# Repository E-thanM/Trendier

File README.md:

# Trendier 👗

A modern fashion social platform for analyzing outfits, discovering trends, and connecting with fashion enthusiasts.

## 🚀 Quick Start

### Option 1: Deploy to Vercel + Supabase (Recommended for Self-Hosting)
See [DEPLOYMENT.md](./DEPLOYMENT.md) for complete self-hosting guide.

### Option 2: Local Development
```bash
# Clone the repository
git clone <YOUR_GIT_URL>
cd trendier

# Install dependencies
npm install

# Copy environment variables
cp .env.example .env
# Edit .env with your Supabase credentials

# Start development server
npm run dev
```

### Option 3: Use Lovable (Original Development Environment)
Visit the [Lovable Project](https://lovable.dev/projects/6f80b55b-fee4-49fe-ab97-270c70876639) and start prompting.

## 📱 Features

- **Outfit Analysis**: AI-powered outfit rating and trend matching
- **Fashion Trends**: Browse and explore current fashion trends with 600+ hashtags
- **Social Feed**: Share outfits and engage with the community
- **Direct Messaging**: Connect with other fashion enthusiasts
- **User Profiles**: Showcase your style and preferences
- **Responsive Design**: Optimized for mobile and desktop

## 🏗️ Tech Stack

**Frontend:**
- React 18 + TypeScript
- Vite (build tool)
- TailwindCSS (styling)
- Shadcn/ui (component library)
- React Router (navigation)
- TanStack Query (data fetching)

**Backend:**
- Supabase (database, auth, storage)
- PostgreSQL (database)
- Row Level Security (RLS)
- Edge Functions (serverless API)

**AI:**
- Lovable AI API (outfit analysis)
- Gemini 2.5 Flash (vision model)

## 📁 Project Structure

```
trendier/
├── src/
│   ├── components/       # React components
│   ├── pages/           # Page components
│   ├── hooks/           # Custom React hooks
│   ├── lib/             # Utility functions
│   ├── integrations/    # Supabase client
│   └── index.css        # Global styles & design tokens
├── supabase/
│   ├── functions/       # Edge functions (backend API)
│   │   ├── analyze-outfit/   # AI outfit analysis
│   │   └── scrape-trends/    # Fashion trend scraper
│   └── migrations/      # Database schema & RLS policies
├── public/              # Static assets
├── DEPLOYMENT.md        # Self-hosting guide
├── vercel.json         # Vercel configuration
└── .env.example        # Environment variables template
```

## 🔧 Environment Variables

Required environment variables (see `.env.example`):

```env
VITE_SUPABASE_PROJECT_ID="your_project_id"
VITE_SUPABASE_URL="https://xxxxx.supabase.co"
VITE_SUPABASE_PUBLISHABLE_KEY="your_anon_key"
```

## 🗄️ Database Schema

All backend code is exposed in the repository:

**Tables** (`supabase/migrations/`):
- `profiles` - User profiles and metadata
- `outfits` - User-uploaded outfit images
- `outfit_likes` - Like/reaction system
- `outfit_comments` - Comment system
- `trends` - Fashion trend data (600+ themes)
- `user_preferences` - User style preferences
- `conversations` & `messages` - Direct messaging

**Edge Functions** (`supabase/functions/`):
- `analyze-outfit` - AI-powered outfit analysis with vision model
- `scrape-trends` - Fashion trend data aggregation

All tables protected with Row Level Security (RLS) policies.

## 🛡️ Security

- ✅ Row Level Security enabled on all tables
- ✅ Anonymous authentication for seamless onboarding
- ✅ Input validation on edge functions (Zod schemas)
- ✅ JWT-based authentication
- ✅ Secure file storage with RLS policies

## 📦 Available Scripts

```bash
npm run dev          # Start development server (localhost:8080)
npm run build        # Build for production
npm run preview      # Preview production build
npm run lint         # Run ESLint
```

## 🌐 Deployment

The app is split into two parts for independent hosting:

1. **Frontend** (Vercel/Netlify/etc): Static React app
2. **Backend** (Supabase): Database, auth, storage, edge functions

### Self-Hosting on Vercel + Supabase

**All backend functions are already exposed in this repository:**
- Database migrations: `supabase/migrations/*.sql`
- Edge functions: `supabase/functions/*/index.ts`
- Auth configuration: In migration files
- Storage policies: In migration files

**Complete deployment guide:** [DEPLOYMENT.md](./DEPLOYMENT.md)

**Quick Steps:**
1. Create your own Supabase project
2. Run migrations to set up database
3. Deploy edge functions to your Supabase project
4. Deploy frontend to Vercel with environment variables
5. Configure auth redirect URLs

### Deploy via Lovable (Easiest)

Simply open [Lovable](https://lovable.dev/projects/6f80b55b-fee4-49fe-ab97-270c70876639) and click Share → Publish.

## 📱 Responsive Design

The app automatically adapts to different screen sizes:

- **Mobile View** (< 768px): 
  - Bottom navigation bar
  - Single-column layout
  - Touch-optimized interactions
  - Mobile-first card designs

- **Desktop View** (≥ 768px):
  - Sidebar navigation
  - Multi-column grid layouts
  - Hover interactions
  - Expanded content display

Vercel (or any static host) serves the built files, and CSS media queries handle responsive behavior automatically.

## 🔌 Backend API Endpoints

When self-hosting, your edge functions will be available at:

```
POST https://YOUR_PROJECT_ID.supabase.co/functions/v1/analyze-outfit
POST https://YOUR_PROJECT_ID.supabase.co/functions/v1/scrape-trends
```

See [DEPLOYMENT.md](./DEPLOYMENT.md) for API documentation and examples.

## 📄 License

This project is open source and available under the MIT License.

## 🤝 Contributing

Contributions are welcome! Please feel free to submit a Pull Request.

## 📞 Support

- **Self-hosting help**: See [DEPLOYMENT.md](./DEPLOYMENT.md)
- **Supabase docs**: [supabase.com/docs](https://supabase.com/docs)
- **Vercel docs**: [vercel.com/docs](https://vercel.com/docs)
- **Lovable docs**: [docs.lovable.dev](https://docs.lovable.dev)

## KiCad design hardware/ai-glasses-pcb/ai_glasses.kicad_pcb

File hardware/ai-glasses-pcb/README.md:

# AI Glasses – Temple PCB

4-layer KiCad project for the electronics in one temple arm of the AI glasses:

- ESP32-S3-WROOM-1 (N16R8)
- DVP camera connector (OV2640 / OV5640)
- I2S MEMS microphone
- USB-C Li-Po charging
- I2S amplifier driving a bone-conduction transducer behind the ear

| File | What it is |
|---|---|
| `ai_glasses.kicad_pro` | open this in KiCad 7+ |
| `ai_glasses.kicad_sch` / `.kicad_pcb` | schematic and routed board |
| `fab/` | Gerbers (+ zip), drill files, pick-and-place, BOM, schematic and assembly PDFs |
| `docs/DESIGN.md` | design notes: shape and anthropometry, power tree, pin map, stack-up, verification, bring-up checklist |
| `VERIFICATION.txt` | output of `scripts/check_design.py` |
| `scripts/` | generators; `design.py` is the single source of truth |

**Note:** the Raspberry Pi Zero camera (MIPI CSI-2) can't connect to an
ESP32-S3. The board uses the pin-compatible-size DVP camera modules instead.
See `docs/DESIGN.md` §2.

## Opening it in KiCad and checking it

1. Install **KiCad 7 or newer**. If you open it in KiCad 8 or 9 and save,
   the files are upgraded and older versions can no longer open them.
2. Open `ai_glasses.kicad_pro`. Keep the whole folder together: the project's
   own symbol/footprint libraries (`AI_Glasses.*`) are found through
   `${KIPRJMOD}`.
3. **Schematic:** Inspect → Electrical Rules Checker → Run ERC. Expect
   0 errors. "Symbol doesn't match library" warnings are harmless; don't
   bulk-update symbols from the library.
4. **PCB:**
   - Press **B** to refill zones.
   - Run **Inspect → Design Rules Checker** with *Refill all zones*
     ticked. Expect 0 errors and 0 unconnected items. The custom rules
     in `ai_glasses.kicad_dru` load automatically.
   - Run **Tools → Update PCB from Schematic** (F8). It should list no
     changes; if it does, cancel.
5. **3D view** (Alt+3): the footprints reference
   `${KICAD7_3DMODEL_DIR}` / `${KICAD6_3DMODEL_DIR}`. On KiCad 8/9, if the
   models are missing, add those names under Preferences → Configure Paths,
   pointing at the same folder as your `KICAD8_`/`KICAD9_3DMODEL_DIR`. This
   only affects the 3D view.
6. **Fab files:** open `fab/gerbers/` in KiCad's Gerber Viewer. To order,
   upload `fab/ai_glasses-gerbers.zip`: 4 layers, 1.0 mm thick,
   1 oz outer / 0.5 oz inner. For assembly, add `fab/ai_glasses-BOM.csv`
   and `fab/ai_glasses-pos.csv`.

### Automated checks (optional)
Needs KiCad's Python module (`pcbnew`) and `pip install sexpdata numpy`.

```
cd scripts
python3 check_design.py   # 600+ checks: netlist match, wiring, links, ERC-style, DRC, placement
python3 check_wiring.py   # schematic wires/labels/no-connects only
```

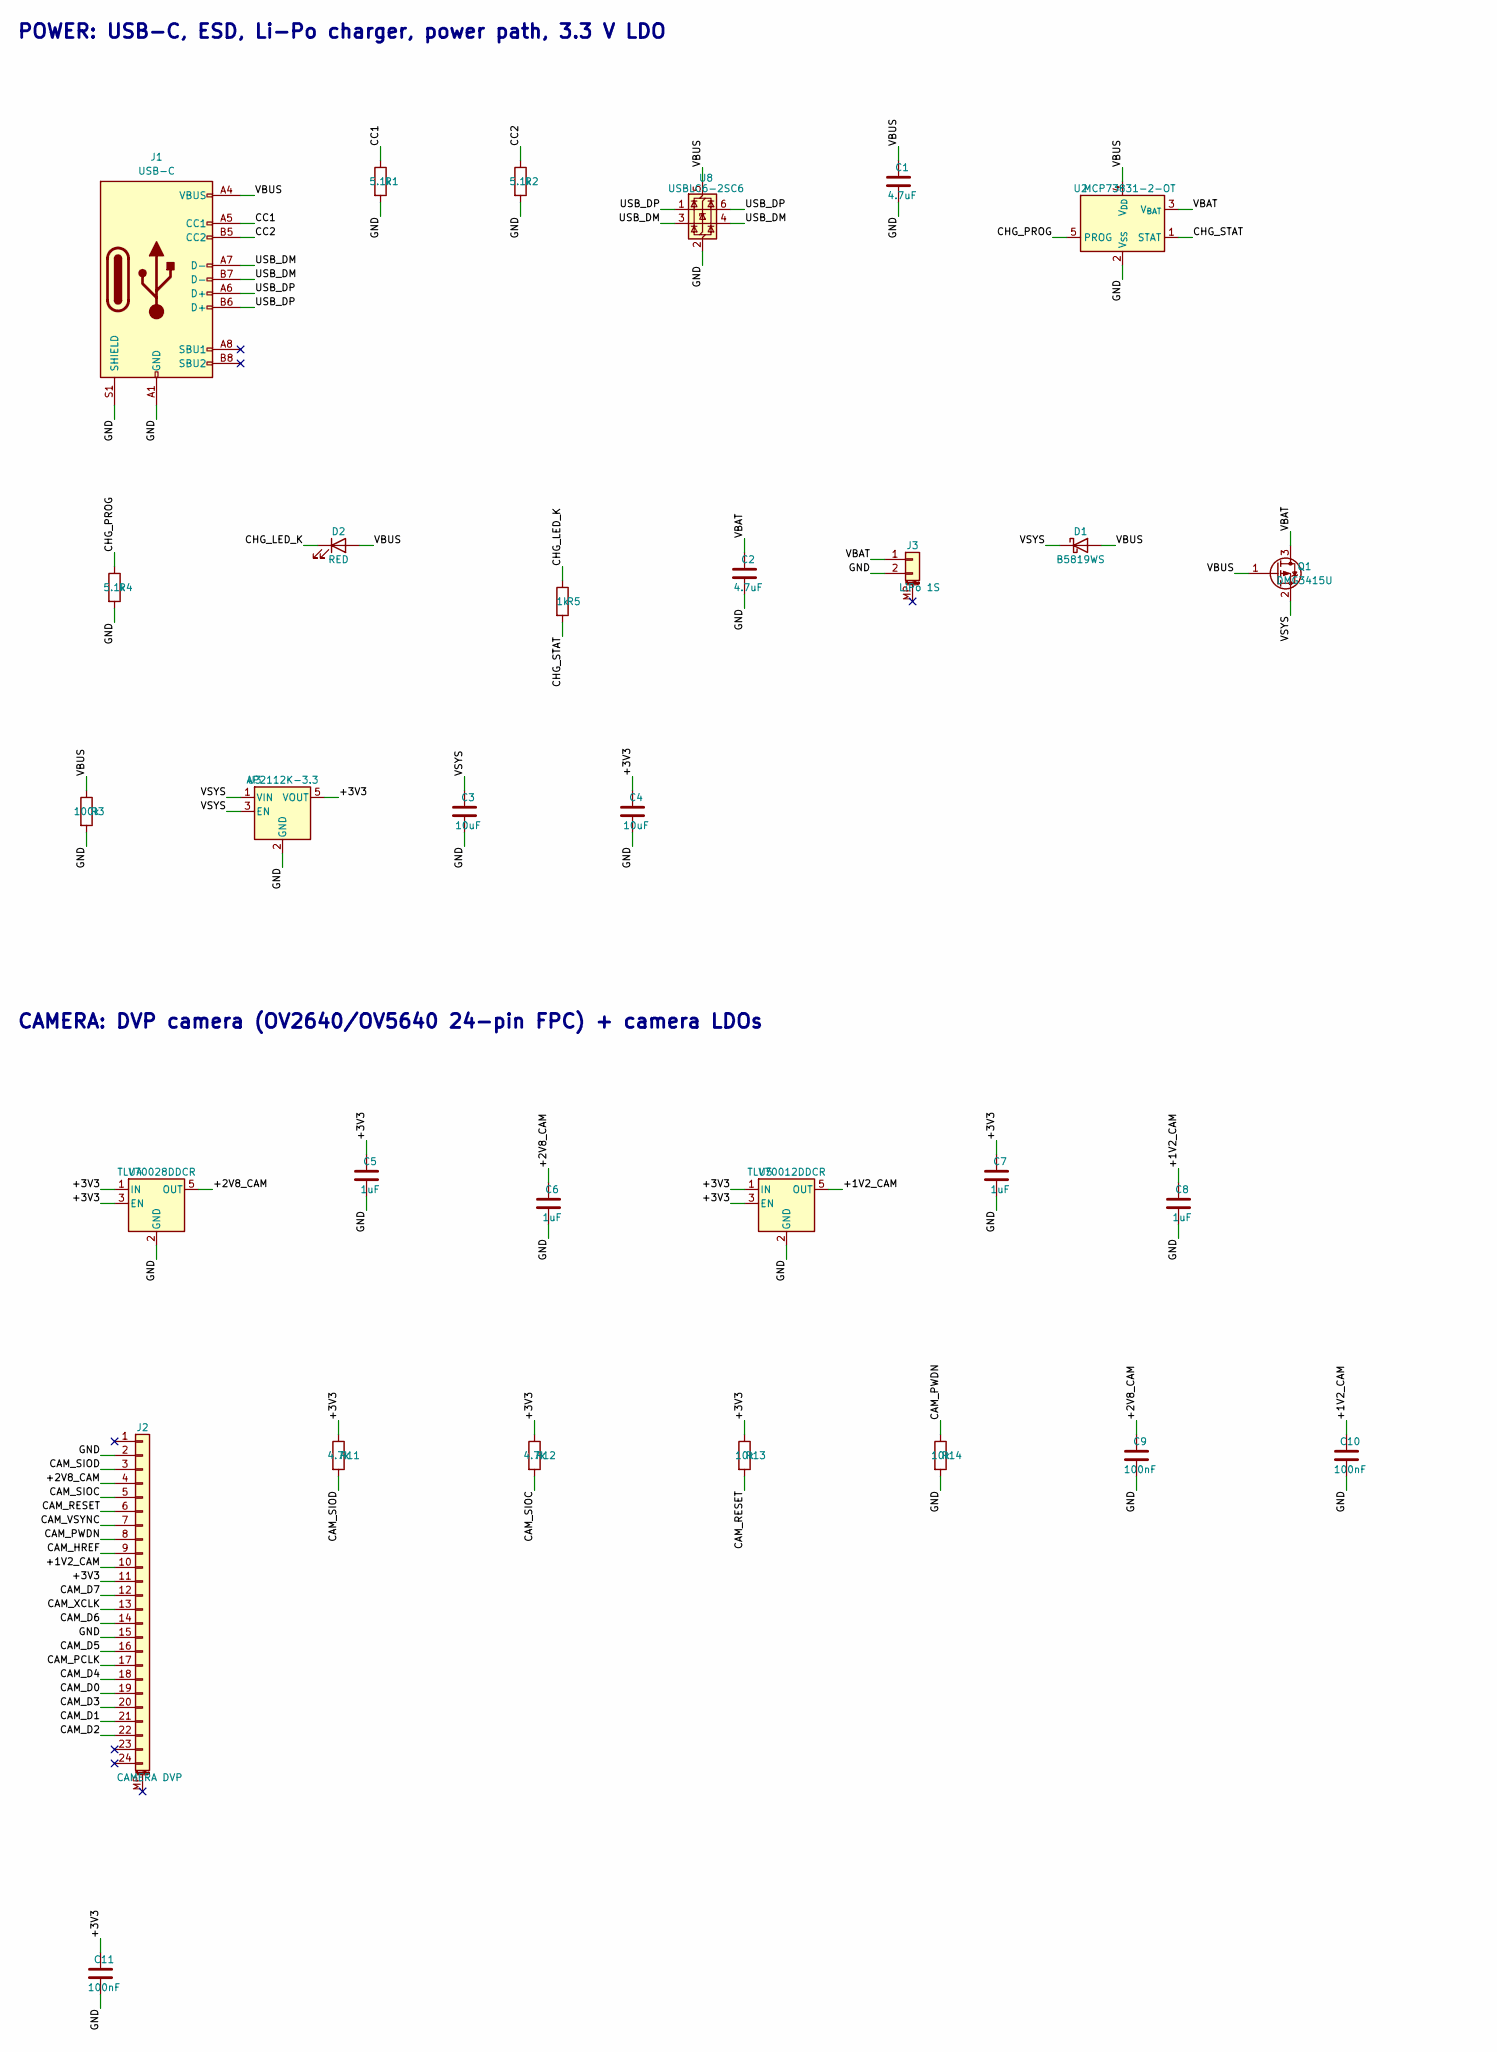
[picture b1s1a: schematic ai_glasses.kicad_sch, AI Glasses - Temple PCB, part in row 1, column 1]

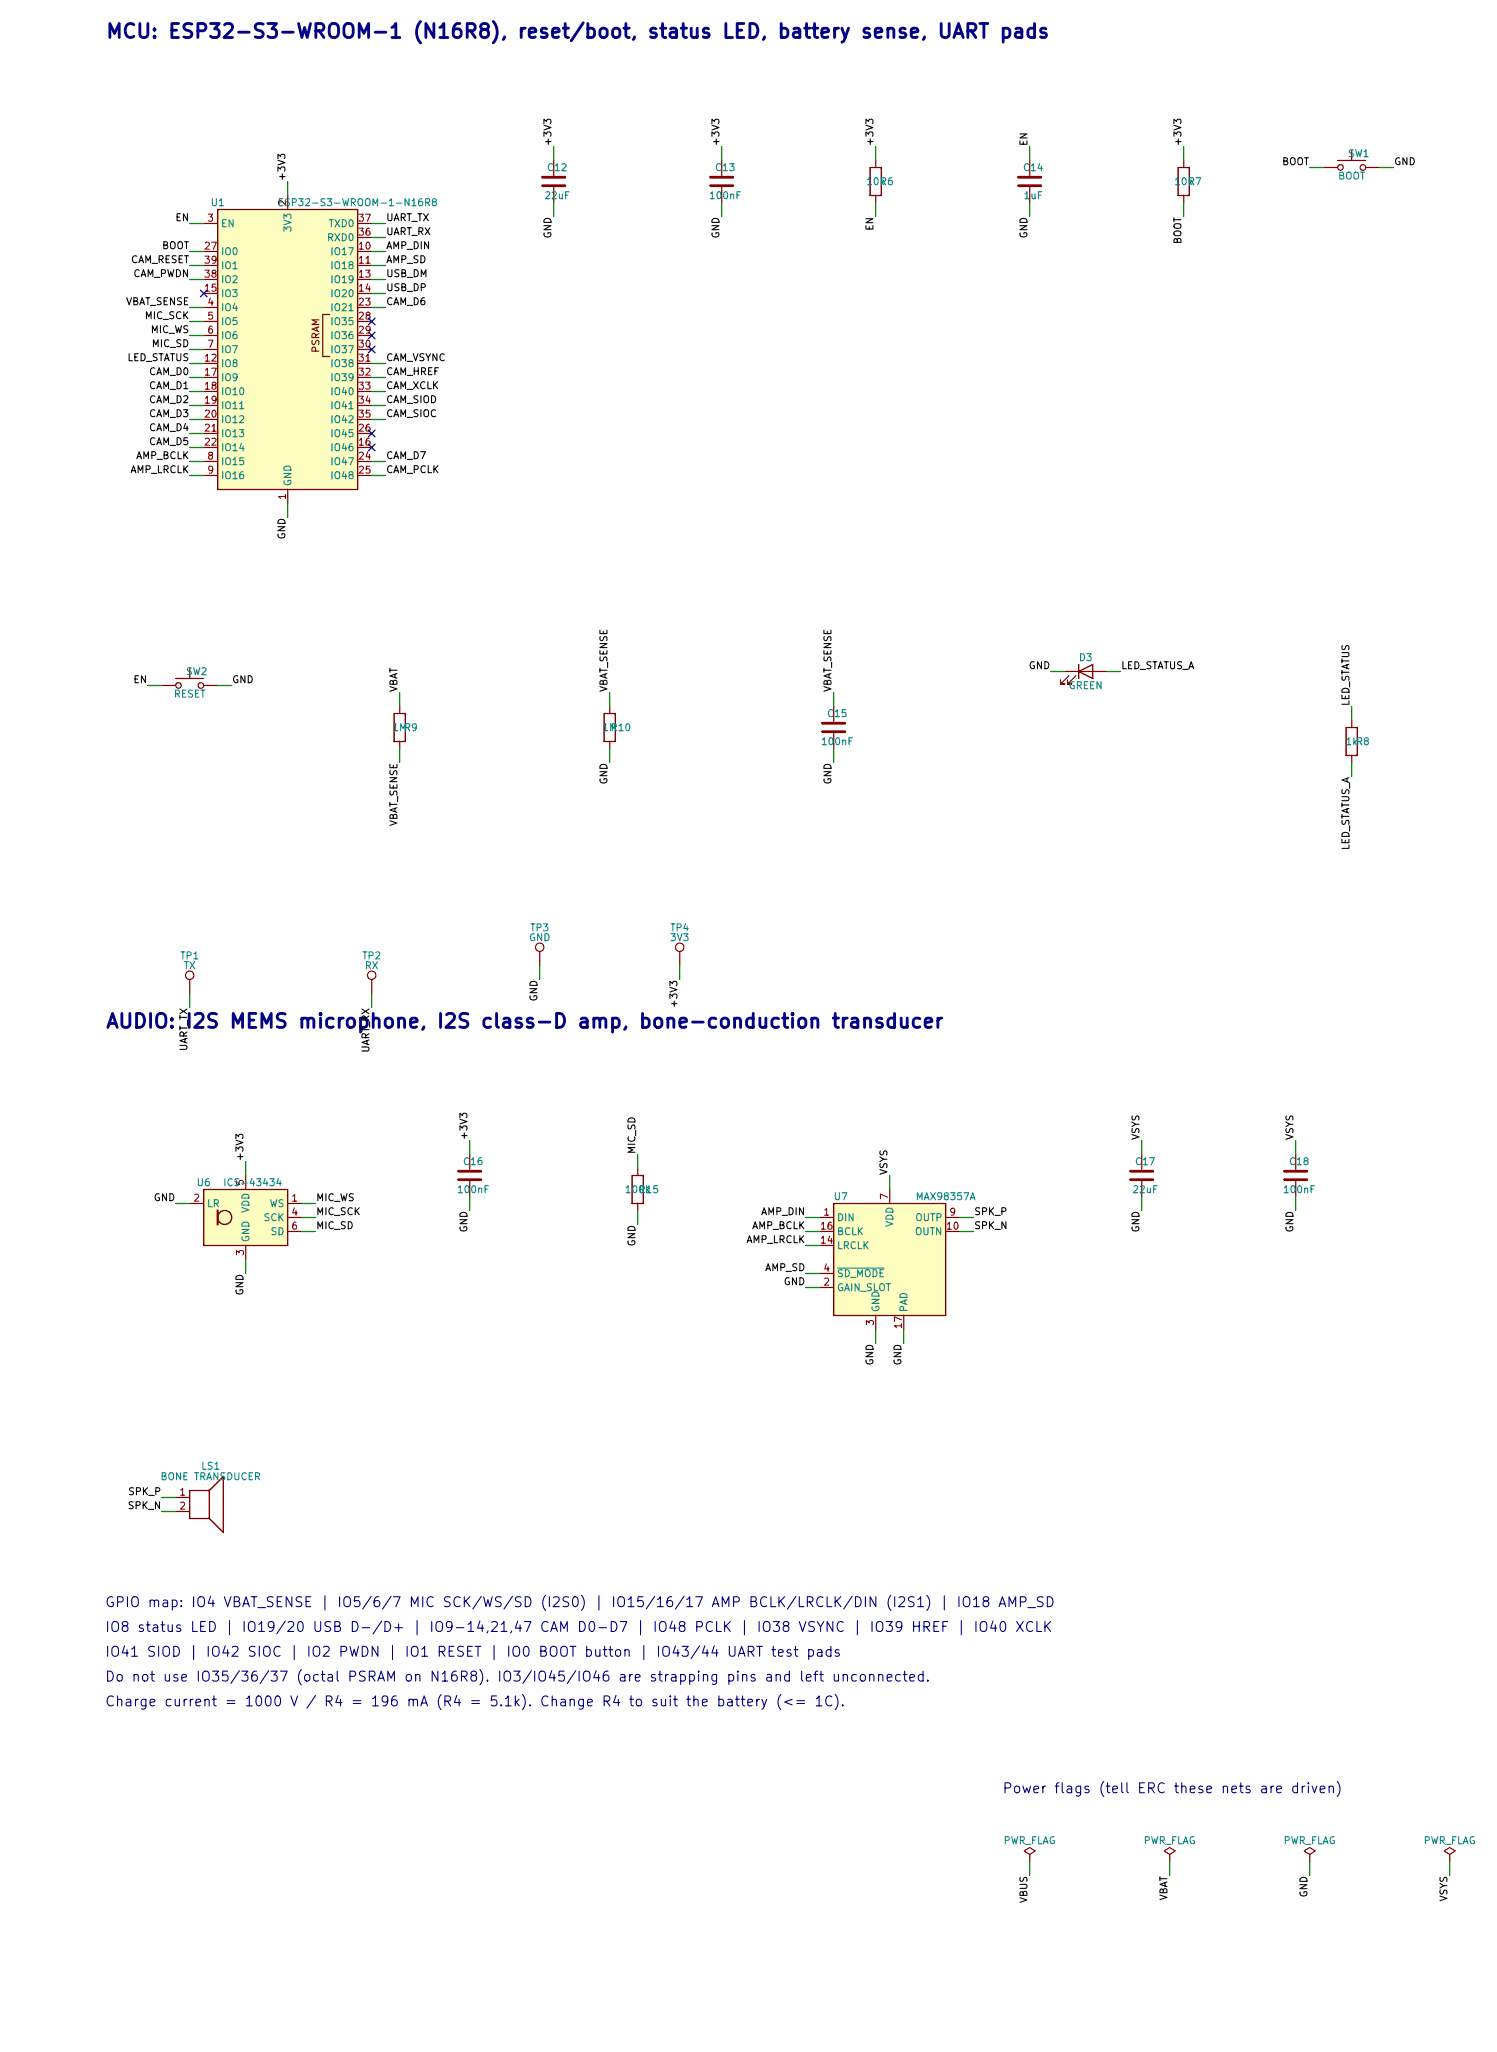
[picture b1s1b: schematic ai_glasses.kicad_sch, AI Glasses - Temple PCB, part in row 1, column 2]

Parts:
C1, C2: 4.7uF; C_0603_1608Metric
C3, C4: 10uF; C_0603_1608Metric
C5, C6, C7, C8, C14: 1uF; C_0402_1005Metric
C9, C10, C11, C13, C15, C16, C18: 100nF; C_0402_1005Metric
C12, C17: 22uF; C_0805_2012Metric
D1: B5819WS; D_SOD-323; MPN B5819WS
D2: RED; LED_0603_1608Metric
D3: GREEN; LED_0603_1608Metric
J1: USB-C; USB_C_Receptacle_GCT_USB4105-xx-A_16P_TopMnt_Horizontal; MPN GCT USB4105-GF-A
J2: CAMERA DVP; Hirose_FH12-24S-0.5SH_1x24-1MP_P0.50mm_Horizontal; MPN Hirose FH12-24S-0.5SH(55)
J3: LiPo 1S; JST_SH_SM02B-SRSS-TB_1x02-1MP_P1.00mm_Horizontal; MPN JST SM02B-SRSS-TB
LS1: BONE TRANSDUCER; BoneTransducer_SolderPads; MPN 8 ohm bone-conduction exciter (e.g. 13x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
Q1: DMG3415U; SOT-23; MPN Diodes DMG3415U-7
R1, R2, R4: 5.1k; R_0402_1005Metric
R3, R15: 100k; R_0402_1005Metric
R5, R8: 1k; R_0402_1005Metric
R6, R7, R13, R14: 10k; R_0402_1005Metric
R9, R10: 1M; R_0402_1005Metric
R11, R12: 4.7k; R_0402_1005Metric
SW1: BOOT; SW_SPST_B3U-1000P; MPN Omron B3U-1000P
SW2: RESET; SW_SPST_B3U-1000P; MPN Omron B3U-1000P
TP1: TX; TestPoint_Pad_D1.0mm
TP2: RX; TestPoint_Pad_D1.0mm
TP3: GND; TestPoint_Pad_D1.0mm
TP4: 3V3; TestPoint_Pad_D1.0mm
U1: ESP32-S3-WROOM-1-N16R8; ESP32-S3-WROOM-1; MPN Espressif ESP32-S3-WROOM-1-N16R8
U2: MCP73831-2-OT; SOT-23-5; MPN Microchip MCP73831T-2ACI/OT
U3: AP2112K-3.3; SOT-23-5; MPN Diodes AP2112K-3.3TRG1
U4: TLV70028DDCR; SOT-23-5; MPN TI TLV70028DDCR
U5: TLV70012DDCR; SOT-23-5; MPN TI TLV70012DDCR
U6: ICS-43434; InvenSense_ICS-43434-6_3.5x2.65mm; MPN TDK InvenSense ICS-43434
U7: MAX98357A; TQFN-16-1EP_3x3mm_P0.5mm_EP1.23x1.23mm_ThermalVias; MPN Analog Devices MAX98357AETE+T
U8: USBLC6-2SC6; SOT-23-6; MPN STMicro USBLC6-2SC6

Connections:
+1V2_CAM: C8.1, C10.1, J2.10, U5.5 (OUT)
+2V8_CAM: C6.1, C9.1, J2.4, U4.5 (OUT)
+3V3: C4.1, C5.1, C7.1, C11.1, C12.1, C13.1, C16.1, J2.11, R6.1, R7.1, R11.1, R12.1, R13.1, TP4.1, U1.2 (3V3), U3.5 (VOUT), U4.1 (IN), U4.3 (EN), U5.1 (IN), U5.3 (EN), U6.5 (VDD)
AMP_BCLK: U1.8 (IO15), U7.16 (BCLK)
AMP_DIN: U1.10 (IO17), U7.1 (DIN)
AMP_LRCLK: U1.9 (IO16), U7.14 (LRCLK)
AMP_SD: U1.11 (IO18), U7.4 (~SD_MODE)
BOOT: R7.2, SW1.1, U1.27 (IO0)
CAM_D0: J2.19, U1.17 (IO9)
CAM_D1: J2.21, U1.18 (IO10)
CAM_D2: J2.22, U1.19 (IO11)
CAM_D3: J2.20, U1.20 (IO12)
CAM_D4: J2.18, U1.21 (IO13)
CAM_D5: J2.16, U1.22 (IO14)
CAM_D6: J2.14, U1.23 (IO21)
CAM_D7: J2.12, U1.24 (IO47)
CAM_HREF: J2.9, U1.32 (IO39)
CAM_PCLK: J2.17, U1.25 (IO48)
CAM_PWDN: J2.8, R14.1, U1.38 (IO2)
CAM_RESET: J2.6, R13.2, U1.39 (IO1)
CAM_SIOC: J2.5, R12.2, U1.35 (IO42)
CAM_SIOD: J2.3, R11.2, U1.34 (IO41)
CAM_VSYNC: J2.7, U1.31 (IO38)
CAM_XCLK: J2.13, U1.33 (IO40)
CC1: J1.A5 (CC1), R1.1
CC2: J1.B5 (CC2), R2.1
CHG_LED_K: D2.1 (K), R5.1
CHG_PROG: R4.1, U2.5 (PROG)
CHG_STAT: R5.2, U2.1 (STAT)
EN: C14.1, R6.2, SW2.1, U1.3 (EN)
GND: C1.2, C2.2, C3.2, C4.2, C5.2, C6.2, C7.2, C8.2, C9.2, C10.2, C11.2, C12.2, C13.2, C14.2, C15.2, C16.2, C17.2, C18.2, D3.1 (K), J1.A1 (GND), J1.A12 (GND), J1.B1 (GND), J1.B12 (GND), J1.S1 (SHIELD), J2.2, J2.15, J3.2, R1.2, R2.2, R3.2, R4.2, R10.2, R14.2, R15.2, SW1.2, SW2.2, TP3.1, U1.1 (GND), U1.40 (GND), U1.41 (GND), U2.2 (V_{SS}), U3.2 (GND), U4.2 (GND), U5.2 (GND), U6.2 (LR), U6.3 (GND), U7.2 (GAIN_SLOT), U7.3 (GND), U7.11 (GND), U7.15 (GND), U7.17 (PAD), U8.2 (GND)
LED_STATUS: R8.1, U1.12 (IO8)
LED_STATUS_A: D3.2 (A), R8.2
MIC_SCK: U1.5 (IO5), U6.4 (SCK)
MIC_SD: R15.1, U1.7 (IO7), U6.6 (SD)
MIC_WS: U1.6 (IO6), U6.1 (WS)
SPK_N: LS1.2, U7.10 (OUTN)
SPK_P: LS1.1, U7.9 (OUTP)
UART_RX: TP2.1, U1.36 (RXD0)
UART_TX: TP1.1, U1.37 (TXD0)
USB_DM: J1.A7 (D-), J1.B7 (D-), U1.13 (IO19), U8.3 (I/O2), U8.4 (I/O2)
USB_DP: J1.A6 (D+), J1.B6 (D+), U1.14 (IO20), U8.1 (I/O1), U8.6 (I/O1)
VBAT: C2.1, J3.1, Q1.3 (D), R9.1, U2.3 (V_{BAT})
VBAT_SENSE: C15.1, R9.2, R10.1, U1.4 (IO4)
VBUS: C1.1, D1.2 (A), D2.2 (A), J1.A4 (VBUS), J1.A9 (VBUS), J1.B4 (VBUS), J1.B9 (VBUS), Q1.1 (G), R3.1, U2.4 (V_{DD}), U8.5 (VBUS)
VSYS: C3.1, C17.1, C18.1, D1.1 (K), Q1.2 (S), U3.1 (VIN), U3.3 (EN), U7.7 (VDD), U7.8 (VDD)

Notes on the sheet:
POWER: USB-C, ESD, Li-Po charger, power path, 3.3 V LDO
MCU: ESP32-S3-WROOM-1 (N16R8), reset/boot, status LED, battery sense, UART pads
CAMERA: DVP camera (OV2640/OV5640 24-pin FPC) + camera LDOs
AUDIO: I2S MEMS microphone, I2S class-D amp, bone-conduction transducer
Power flags (tell ERC these nets are driven)
GPIO map: IO4 VBAT_SENSE | IO5/6/7 MIC SCK/WS/SD (I2S0) | IO15/16/17 AMP BCLK/LRCLK/DIN (I2S1) | IO18 AMP_SD
IO8 status LED | IO19/20 USB D-/D+ | IO9-14,21,47 CAM D0-D7 | IO48 PCLK | IO38 VSYNC | IO39 HREF | IO40 XCLK
IO41 SIOD | IO42 SIOC | IO2 PWDN | IO1 RESET | IO0 BOOT button | IO43/44 UART test pads
Do not use IO35/36/37 (octal PSRAM on N16R8). IO3/IO45/IO46 are strapping pins and left unconnected.
Charge current = 1000 V / R4 = 196 mA (R4 = 5.1k). Change R4 to suit the battery (<= 1C).

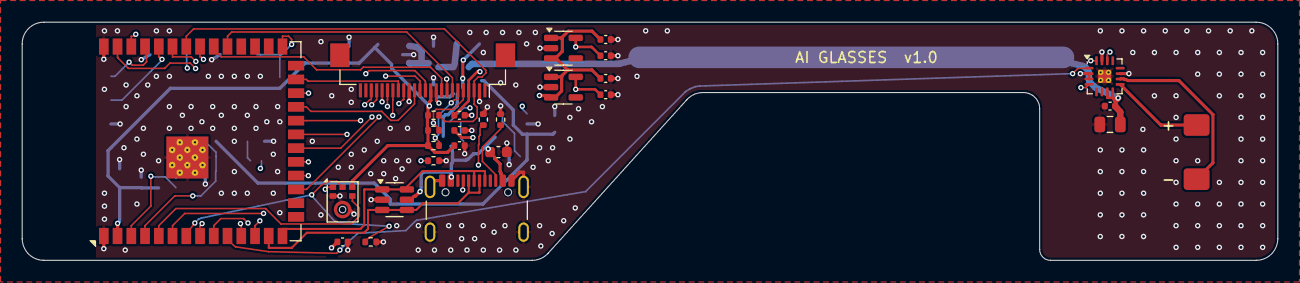
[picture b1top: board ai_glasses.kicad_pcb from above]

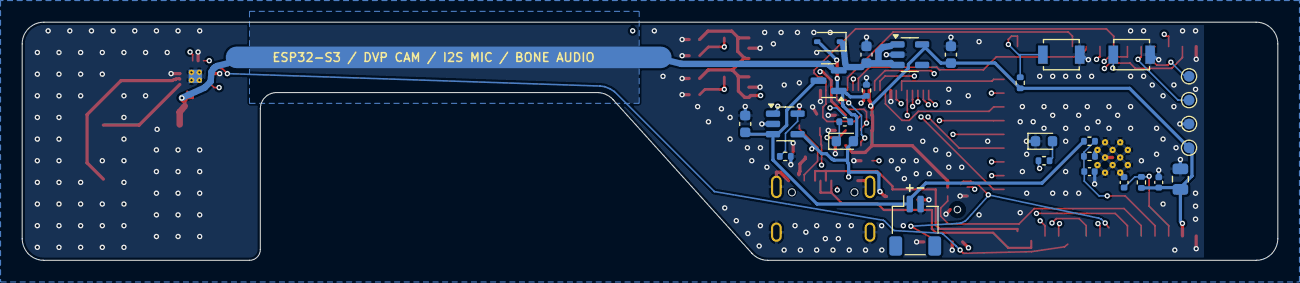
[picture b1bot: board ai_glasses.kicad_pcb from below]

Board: 4 copper layers, 116.0 x 22.0 mm, 55 parts (28 on the bottom side), 46 nets.

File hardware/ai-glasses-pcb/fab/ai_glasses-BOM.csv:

Qty,References,Value,Footprint,Part / MPN,Side,Notes
2,C1 C2,4.7uF,C_0603_1608Metric,"X5R/X7R MLCC, >= 10 V",Bottom/Top,
2,C12 C17,22uF,C_0805_2012Metric,"X5R/X7R MLCC, >= 10 V",Bottom/Top,
7,C9 C10 C11 C13 C15 C16 C18,100nF,C_0402_1005Metric,"X5R/X7R MLCC, >= 10 V",Bottom/Top,
2,C3 C4,10uF,C_0603_1608Metric,"X5R/X7R MLCC, >= 10 V",Bottom,
5,C5 C6 C7 C8 C14,1uF,C_0402_1005Metric,"X5R/X7R MLCC, >= 10 V",Bottom/Top,
1,D1,B5819WS,D_SOD-323,B5819WS,Bottom,USB -> system power path
1,D2,RED,LED_0603_1608Metric,0603 LED,Bottom,Charging indicator
1,D3,GREEN,LED_0603_1608Metric,0603 LED,Bottom,Status LED
1,J1,USB-C,USB_C_Receptacle_GCT_USB4105-xx-A_16P_TopMnt_Horizontal,GCT USB4105-GF-A,Top,"USB-C 2.0 receptacle, charging + native USB programming"
1,J2,CAMERA DVP,Hirose_FH12-24S-0.5SH_1x24-1MP_P0.50mm_Horizontal,Hirose FH12-24S-0.5SH(55),Top,24-pin 0.5 mm FPC for OV2640 / OV5640 DVP camera
1,J3,LiPo 1S,JST_SH_SM02B-SRSS-TB_1x02-1MP_P1.00mm_Horizontal,JST SM02B-SRSS-TB,Bottom,"Battery connector (JST-SH 1 mm). Pin1 = +, Pin2 = -"
1,LS1,BONE TRANSDUCER,BoneTransducer_SolderPads,"8 ohm bone-conduction exciter (e.g. 13x13 mm, 1 W)",Top,Bone conduction transducer solder pads
1,Q1,DMG3415U,SOT-23,Diodes DMG3415U-7,Bottom,Battery -> system ideal-diode switch (off when USB present)
3,R1 R2 R4,5.1k,R_0402_1005Metric,"Yageo RC0402FR-07 series (1%, 1/16 W)",Bottom/Top,
2,R11 R12,4.7k,R_0402_1005Metric,"Yageo RC0402FR-07 series (1%, 1/16 W)",Top,
2,R3 R15,100k,R_0402_1005Metric,"Yageo RC0402FR-07 series (1%, 1/16 W)",Bottom/Top,
2,R5 R8,1k,R_0402_1005Metric,"Yageo RC0402FR-07 series (1%, 1/16 W)",Bottom,
4,R6 R7 R13 R14,10k,R_0402_1005Metric,"Yageo RC0402FR-07 series (1%, 1/16 W)",Bottom/Top,
2,R9 R10,1M,R_0402_1005Metric,"Yageo RC0402FR-07 series (1%, 1/16 W)",Bottom,
1,SW1,BOOT,SW_SPST_B3U-1000P,Omron B3U-1000P,Bottom,Boot / user button (IO0)
1,SW2,RESET,SW_SPST_B3U-1000P,Omron B3U-1000P,Bottom,Reset button (EN)
1,TP1,TX,TestPoint_Pad_D1.0mm,(bare pad - not assembled),Bottom,UART0 TX test pad
1,TP2,RX,TestPoint_Pad_D1.0mm,(bare pad - not assembled),Bottom,UART0 RX test pad
1,TP3,GND,TestPoint_Pad_D1.0mm,(bare pad - not assembled),Bottom,GND test pad
1,TP4,3V3,TestPoint_Pad_D1.0mm,(bare pad - not assembled),Bottom,3V3 test pad
1,U1,ESP32-S3-WROOM-1-N16R8,ESP32-S3-WROOM-1,Espressif ESP32-S3-WROOM-1-N16R8,Top,"Wi-Fi/BLE MCU, 16 MB flash, 8 MB octal PSRAM"
1,U2,MCP73831-2-OT,SOT-23-5,Microchip MCP73831T-2ACI/OT,Bottom,"Single-cell Li-Po charger, 196 mA (R4)"
1,U3,AP2112K-3.3,SOT-23-5,Diodes AP2112K-3.3TRG1,Bottom,3.3 V / 600 mA main LDO
1,U4,TLV70028DDCR,SOT-23-5,TI TLV70028DDCR,Top,Camera AVDD 2.8 V LDO
1,U5,TLV70012DDCR,SOT-23-5,TI TLV70012DDCR,Top,Camera DVDD 1.2 V LDO
1,U6,ICS-43434,InvenSense_ICS-43434-6_3.5x2.65mm,TDK InvenSense ICS-43434,Top,"I2S MEMS microphone, bottom port (hole through PCB)"
1,U7,MAX98357A,TQFN-16-1EP_3x3mm_P0.5mm_EP1.23x1.23mm_ThermalVias,Analog Devices MAX98357AETE+T,Top,"3.2 W I2S class-D amplifier, gain 12 dB (GAIN_SLOT to GND)"
1,U8,USBLC6-2SC6,SOT-23-6,STMicro USBLC6-2SC6,Top,USB ESD protection

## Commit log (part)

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2025-11-05 [skip lovable] Use tech stack vite_react_shadcn_ts_20250728_minor
2025-11-05 Refactor UI for modern look
2025-11-07 Refactor: Implement AI analysis and update styling
    This commit introduces AI-powered outfit analysis and refactors the application's styling to be more modern and professional.
    Key changes include:
    - **Color Scheme Update**: Implemented a complementary green and blue color scheme in `src/index.css` for a sleeker, more professional look.
    - **AI Outfit Analysis**: Integrated Lovable AI for outfit analysis. The `analyze-outfit` edge function now processes uploaded images and provides ratings, trend matches, and style analysis.
    - **Trend Scraper**: Implemented a `scrape-trends` edge function to fetch and store current fashion trends, which are then used by the AI analyzer.
    - **Profile Page Enha
2025-11-07 Enhance feed with Instagram-like features
    Add stories bar, double-tap to like functionality, and improve outfit card display to mimic Instagram's feed experience. Also includes a fix for a build error by adding the `react-is` dependency.
2025-11-07 Implement comment and share functionality
    Add functionality to the comment and share buttons on outfit posts. This includes creating a `CommentsDrawer` component for viewing and adding comments, and a `ShareDialog` component for sharing opti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
2025-11-07 Position comments dialog at bottom
    Move the floating comments dialog to the bottom of the screen for desktop users. The dialog maintains a compact and visually appealing design.
2025-11-07 Align headers at the top
    Align the sidebar header with the main header to ensure they align at the top when scrolled. This involves setting a consistent height and vertical alignment for both elements.
2025-11-07 Refactor settings tab
    Switch up the settings tab to include account information, contact us form, and privacy preferences. This refactor provides a more intuitive and valuable user experience.
2025-11-07 Hide FeedHeader on desktop, add messages/notifications to settings
    The FeedHeader component is now hidden on desktop screens (`md:hidden`) and will only appear on mobile devices. The messages and notifications sections have been integrated into the `SettingsSheet` c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
2025-11-07 Refactor messages page layout and functionality
    Improve spacing on the messages page to fit perfectly on a single desktop view. Make the send button functional, allowing users to send messages within a conversation.
2025-11-07 Fix messaging error and make survey collapsible
    The RLS policy for conversation_participants was causing infinite recursion, which has been fixed. The PreferencesSurvey component has been made collapsible, with a button to start the quiz. The surv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
2025-11-07 Implement followers section and public followers setting
    This commit introduces the followers section, allowing users to view their followers and who they are following. It also adds a setting to control the visibility of followers, making the section publ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
2025-11-07 Fix settings icon positioning
    Adjust the flex alignment and positioning of the settings icon on the profile page to ensure it is correctly aligned with other profile elements.
2025-11-07 Fix security vulnerabilities
    Add input validation and email redirect configuration to address security vulnerabilities.
2025-11-07 Fix settings icon positioning
    Adjusted the layout of the profile header to ensure the settings icon remains correctly positioned and constrained within its container, preventing it from appearing out of place on the right side.
2025-11-07 Update site info
    Edited UI in Lovable
2025-11-07 Add duplicate username/email validation
    Add validation to the login page to check for existing usernames and emails before account creation. If a duplicate is found, a user-friendly toast message will be displayed.
2025-11-07 Fix flickering messages and RLS policy
    The AI addressed critical issues in the messaging feature:
    - Resolved button nesting errors in `src/pages/Messages.tsx` that caused message flickering and disappearing.
    - Updated the RLS policy for the `conversations` table to `FOR INSERT TO authenticated WITH CHECK (auth.uid() IS NOT NULL)` to ensure users can create conversations.
    - Added a "Back" button to the messages page to allow users to exit problematic conversations.
2025-11-07 Fix message creation RLS policy
    Implemented a SECURITY DEFINER function `create_conversation_for_users` to handle conversation creation. This function bypasses RLS policies for the `conversations` table but includes internal checks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
2025-11-07 Add fullscreen image viewer
    Implement a fullscreen image viewer for outfit posts, similar to Instagram's functionality. This includes creating a new `FullscreenImageViewer` component and integrating it into the `OutfitCard` com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
2025-11-08 Add X button to trend chart popup
    Add an X button to the trend detail modal to allow users to close the popup charts. The button is styled similarly to the one in `FullscreenImageViewer.tsx` and is positioned in the top-right corner 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
2025-11-08 Add clickable hashtags to Analyzer page
    Implement functionality to make hashtags on the Analyzer page clickable. Clicking a hashtag will now fetch detailed trend information from the database and display it in a modal using the existing Tr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
2025-11-08 Expand trend tracking and enable real-time updates
    This commit expands the list of tracked fashion hashtags in the scraper to over 100, providing more comprehensive data research and topics. It also enables real-time updates for the trends section by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
2025-11-08 Fix guest profile page display
    Ensure sign up/login prompts are displayed for guests and unauthenticated users when they attempt to access the profile page. This resolves an issue where these users might see a blank page or an inc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
2025-11-09 Fix vertical alignment in sidebar
    Ensure consistent vertical alignment and height for all sidebar menu items by removing the SidebarMenuButton wrapper and applying uniform styling directly to the elements. This resolves lingering ver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
2025-11-09 Fix security vulnerabilities
    Address critical security issues including an unprotected edge function, authentication bypass via guest mode, and missing input validation in the analyze-outfit function.
2025-11-09 Make bottom nav highlight constant
    Ensure the active tab in the mobile bottom navigation bar is always highlighted green, regardless of hover state. This change applies consistent styling to all navigation items based on the current r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
2025-11-09 Add caching to trend scraper
    Implement a caching mechanism for the trend scraper to store discovered trends for 7 days. This reduces the need for frequent Serper API calls and preserves the request quota.
    Additionally, this commit addresses the user's concern about no API usage being detected on Serper. It clarifies that the "analyzer feature" is for user outfit photos and is separate from the trend s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
2025-11-09 Add error handling to analyze-outfit function
    Improve error handling in the analyze-outfit edge function to provide more detailed logs when API calls fail. This will help in diagnosing issues with Gemini API responses for search term extraction 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
2025-11-10 Add profile picture upload
    Enable uploading and displaying a profile avatar
    - Integrates avatar upload flow on /profile
    - Adds storage-backed avatar upload using Supabase
    - Updates Profile UI to show and replace avatar
    - Includes removal of old avatar and update to user profile avatar_url
2025-11-10 Mark unread badge read
    Improve unread badge handling by updating markAsRead to rely on latest message timestamp and propagate reads more reliably. Ensures badge disappears when all conversations are viewed and prepares bac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
2025-11-10 Update analyzer to 100-point scale
    Converts backend rating from 1-10 to 1-100 and updates analyzer to display /100 accordingly. Adjusts edge function prompt and rate handling to align with the new scale.
2025-11-10 Link TikTok trends with photo analyzer
    Integrate TikTok trend data into the outfit analyzer by:
    - Fetching current TikTok trend items from the tiktok_videos and tiktok_detected_items tables
    - Calculating and displaying a TikTok trend match score for outfits
    - Showing matching TikTok items and example videos alongside analyzer results
    - Extending Analyzer.tsx UI to present TikTok trend data and matches
    - Ensuring seamless UX when cross-referencing trends with uploaded photos
2025-11-10 Set up automated TikTok Scraping
    Implement cron-based background scraping, verify real video content analysis, speed up analyzer, merge UI, and complete end-to-end testing for TikTok trends integration.
2025-11-10 Fix base64 conversion loop in outfit analyzer
    Replace problematic base64 conversion using spread operator with iterative byte-to-base64 encoding in analyze-outfit to prevent stack overflow on large images; deploy fixed edge function and ensure n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
2025-11-10 Improve TikTok video data usage and Google Trends UI
2025-11-10 Reduce TikTok visual match to 3 videos; add content filter and streamline UI with 3-4 boxes plus outfit pairing recommendation
    Adjust analyze-outfit to:
    - Limit TikTok visual analysis to top 3 candidates for faster processing
    - Filter out inappropriate content from TikTok results
    - Simplify UI to 3-4 metric boxes and add a recommended pairing section
    - Ensure safe, relevant TikTok links and provide concise results
    Frontend Analyzer UI updated to reflect reduced display and include pairing recommendation.
2025-11-10 Fix shopping links and verify video library
2025-11-11 Restore and simplify outfit analysis queue
    - Repaired analyze-outfit edge function by removing corrupted/refactored queue logic
    - Reinstated working serve() flow with valid TypeScript, ensuring parsing succeeds
    - Added a minimal queue implementation via outfit_analysis_queue table
    - Wired frontend polling to queue status; maintainable, incremental approach avoiding in-function complex concurrency
    - Deployed updated edge function and ensured integration with queue table
2025-11-11 Expand TikTok scraper and automate refresh
    - Reduce cache window to 6 hours for TikTok trends
    - Introduce automatic background scraping of common fashion hashtags every 2 hours
    - Improve scraper robustness: skip videos with invalid thumbnails, avoid bootstrap data, and return empty on total failure
    - Deploy updated edge functions and initiate initial scrape to seed database
2025-11-11 Improve robust TikTok scraper resilience
    Implement multi-strategy adaptive TikTok scraper with fallback paths (oembed-based discovery, mobile API attempts, creator profiling), enhance health checks, and force redeploys to maintain uptime am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
2025-11-12 Add crown and vomit effects
    Enhance profile visuals with conditional decorations:
    - Show crown above avatar and pulsing effect when viewing own profile
    - Display animated vomit emojis around avatar when viewing Benji's profile
    - Implemented entirely in src/pages/Profile.tsx to affect only the profile header/avatar area based on isOwnProfile and username checks
